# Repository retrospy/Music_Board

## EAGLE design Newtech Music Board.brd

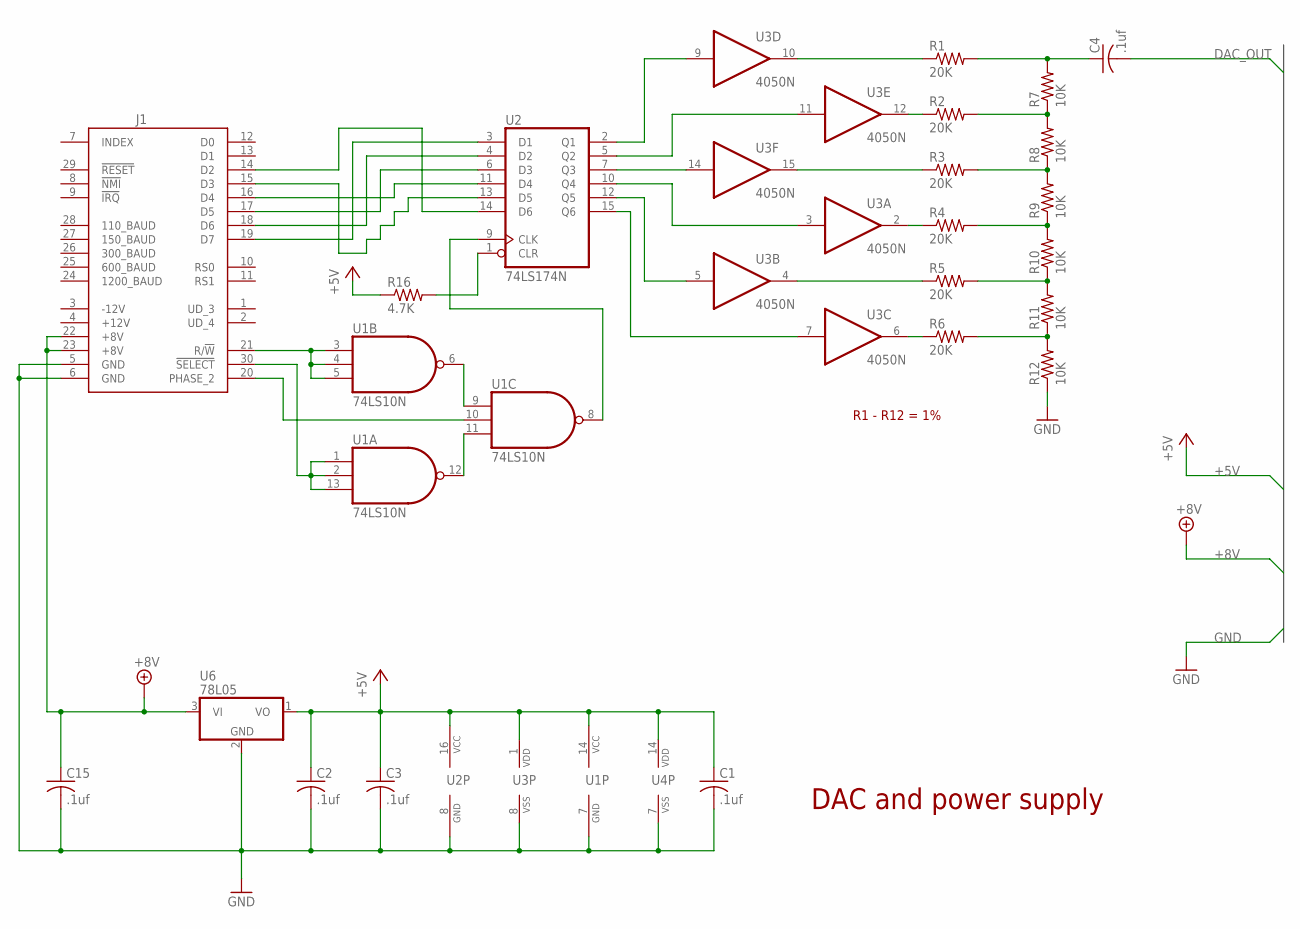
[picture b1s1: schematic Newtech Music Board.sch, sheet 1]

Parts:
C1, C2, C3, C15: .1uf; C025-025X050
C4: .1uf; C025-024X044
J1: SS-30_BOARD_CONNECTOR
R1, R2, R3, R4, R5, R6: 20K; 0204/7
R7, R8, R9, R10, R11, R12: 10K; 0204/7
R16: 4.7K; 0204/7
U1: 74LS10N; DIL14
U2: 74LS174N; DIL16
U3: 4050N; DIL16
U4: 4069N; DIL14
U6: 78L05; TO-92

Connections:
!SELECT: J1.30 (!SELECT), U1.1 (I0), U1.2 (I1), U1.13 (I2)
+5V: C1.1, C2.1, C3.1, R16.1, U1.14 (VCC), U2.16 (VCC), U3.1 (VDD), U4.14 (VDD), U6.1 (VO)
+8V: C15.1, J1.22 (+8V), J1.23 (+8V), U6.3 (VI); also elsewhere on the board
+12V: J1.4 (+12V)
-12V: J1.3 (-12V)
DAC_OUT: C4.2; also elsewhere on the board
GND: C1.2, C2.2, C3.2, C15.2, J1.5 (GND), J1.6 (GND), R12.1, U1.7 (GND), U2.8 (GND), U3.8 (VSS), U4.7 (VSS), U6.2 (GND); also elsewhere on the board
unnamed: J1.19 (D7), U2.3 (D1)
unnamed: J1.18 (D6), U2.4 (D2)
unnamed: J1.17 (D5), U2.6 (D3)
unnamed: U1.6 (O), U1.9 (I0)
unnamed: U1.11 (I2), U1.12 (O)
unnamed: J1.16 (D4), U2.11 (D4)
unnamed: J1.15 (D3), U2.13 (D5)
unnamed: J1.14 (D2), U2.14 (D6)
unnamed: U2.2 (Q1), U3.9 (I)
unnamed: U2.5 (Q2), U3.11 (I)
unnamed: U2.7 (Q3), U3.14 (I)
unnamed: U2.10 (Q4), U3.3 (I)
unnamed: U2.12 (Q5), U3.5 (I)
unnamed: U2.15 (Q6), U3.7 (I)
unnamed: U1.8 (O), U2.9 (CLK)
unnamed: R16.2, U2.1 (CLR)
unnamed: R1.1, U3.10 (O)
unnamed: R2.1, U3.12 (O)
unnamed: R3.1, U3.15 (O)
unnamed: R4.1, U3.2 (O)
unnamed: R5.1, U3.4 (O)
unnamed: R6.1, U3.6 (O)
unnamed: R2.2, R7.1, R8.2
unnamed: R3.2, R8.1, R9.2
unnamed: R4.2, R9.1, R10.2
unnamed: R5.2, R10.1, R11.2
unnamed: R6.2, R11.1, R12.2
unnamed: C4.1, R1.2, R7.2
PHASE2: J1.20 (PHASE_2), U1.10 (I1)
R/!W: J1.21 (R/!W), U1.3 (I0), U1.4 (I1), U1.5 (I2)

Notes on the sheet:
DAC and power supply
R1 - R12 = 1%

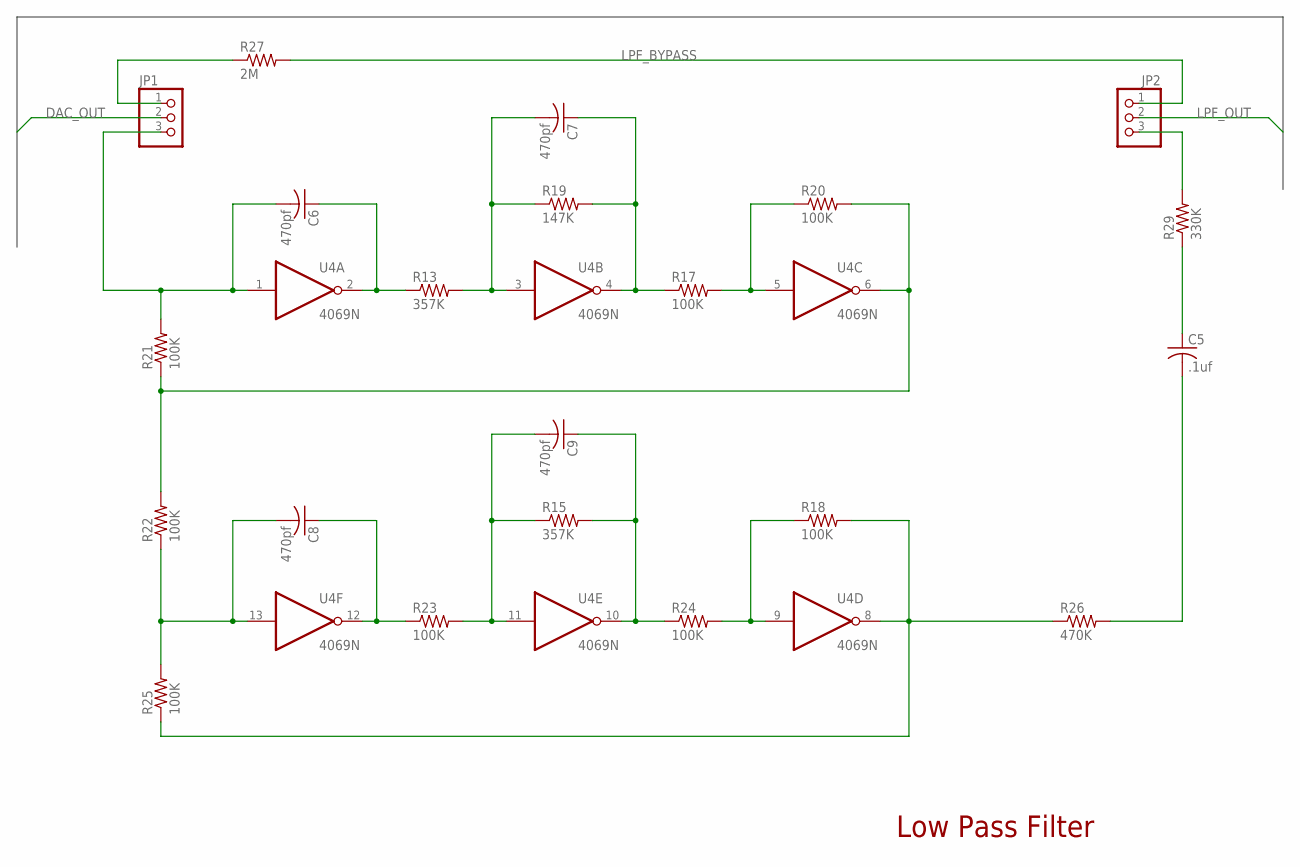
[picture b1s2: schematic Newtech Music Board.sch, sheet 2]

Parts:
C5: .1uf; C025-025X050
C6, C7, C8, C9: 470pf; C050-045X075
JP1, JP2: PINHD-1X3; 1X03
R13, R15: 357K; 0204/7
R17, R18, R20, R21, R22, R23, R24, R25: 100K; 0204/7
R19: 147K; 0204/7
R26: 470K; 0204/7
R27: 2M; 0204/7
R29: 330K; 0204/7
U4: 4069N; DIL14

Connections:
DAC_OUT: JP1.2; also elsewhere on the board
LPF_BYPASS: JP2.1, R27.2
LPF_OUT: JP2.2; also elsewhere on the board
unnamed: C6.2, JP1.3, R21.2, U4.1 (I)
unnamed: JP2.3, R29.2
unnamed: C6.1, R13.1, U4.2 (O)
unnamed: C7.2, R13.2, R19.1, U4.3 (I)
unnamed: C7.1, R17.1, R19.2, U4.4 (O)
unnamed: R17.2, R20.1, U4.5 (I)
unnamed: R20.2, R21.1, R22.2, U4.6 (O)
unnamed: JP1.1, R27.1
unnamed: C8.1, R23.1, U4.12 (O)
unnamed: C9.2, R15.1, R23.2, U4.11 (I)
unnamed: C9.1, R15.2, R24.1, U4.10 (O)
unnamed: R18.1, R24.2, U4.9 (I)
unnamed: R18.2, R25.1, R26.1, U4.8 (O)
unnamed: C5.2, R26.2
unnamed: C5.1, R29.1
unnamed: C8.2, R22.1, R25.2, U4.13 (I)

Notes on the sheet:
Low Pass Filter

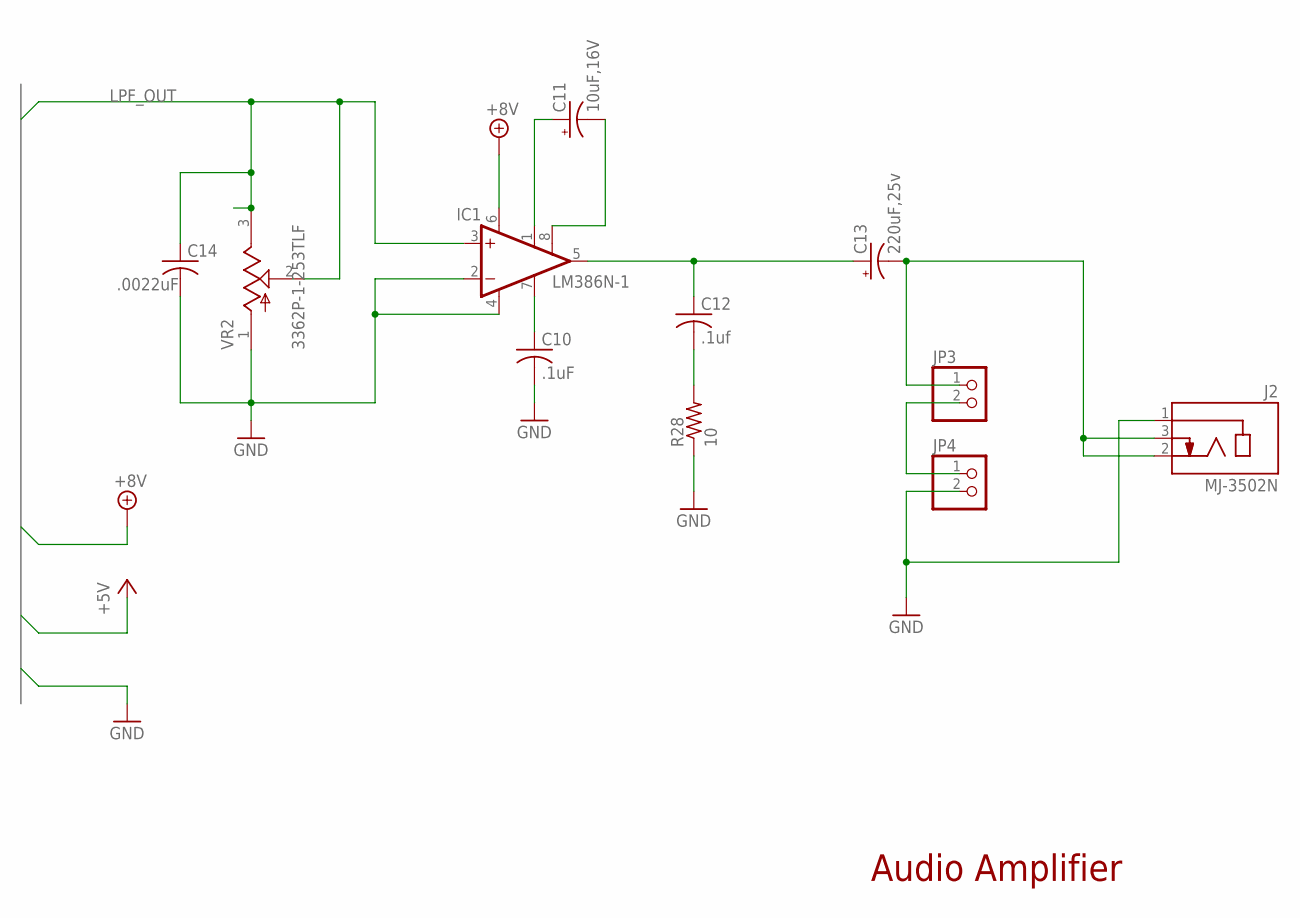
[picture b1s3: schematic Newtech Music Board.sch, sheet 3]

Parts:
C10: .1uF; C025-025X050
C11: 10uF,16V; E2,5-6
C12: .1uf; C025-025X050
C13: 220uF,25v; E25-9
C14: .0022uF; C025-025X050
IC1: LM386N-1; DIL08
J2: MJ-3502N; CUI_MJ-3502N
JP3, JP4: PINHD-1X2; 1X02
R28: 10; 0204/7
VR2: 3362P-1-253TLF; TRIM_3362P-1-253TLF

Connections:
+8V: IC1.6 (VS); also elsewhere on the board
GND: C10.2, C14.2, IC1.2 (-IN), IC1.4 (GND), J2.1, JP4.2, R28.1, VR2.1 (CCW); also elsewhere on the board
LPF_OUT: C14.1, IC1.3 (+IN), VR2.2 (WIPER), VR2.3 (CW); also elsewhere on the board
unnamed: JP3.2, JP4.1
unnamed: C10.1, IC1.7 (BYPASS)
unnamed: C12.2, R28.2
unnamed: C11.+, IC1.1 (GAIN)
unnamed: C12.1, C13.+, IC1.5 (OUT)
unnamed: C13.-, J2.2, J2.3, JP3.1
unnamed: C11.-, IC1.8 (GAIN)

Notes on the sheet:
Audio Amplifier

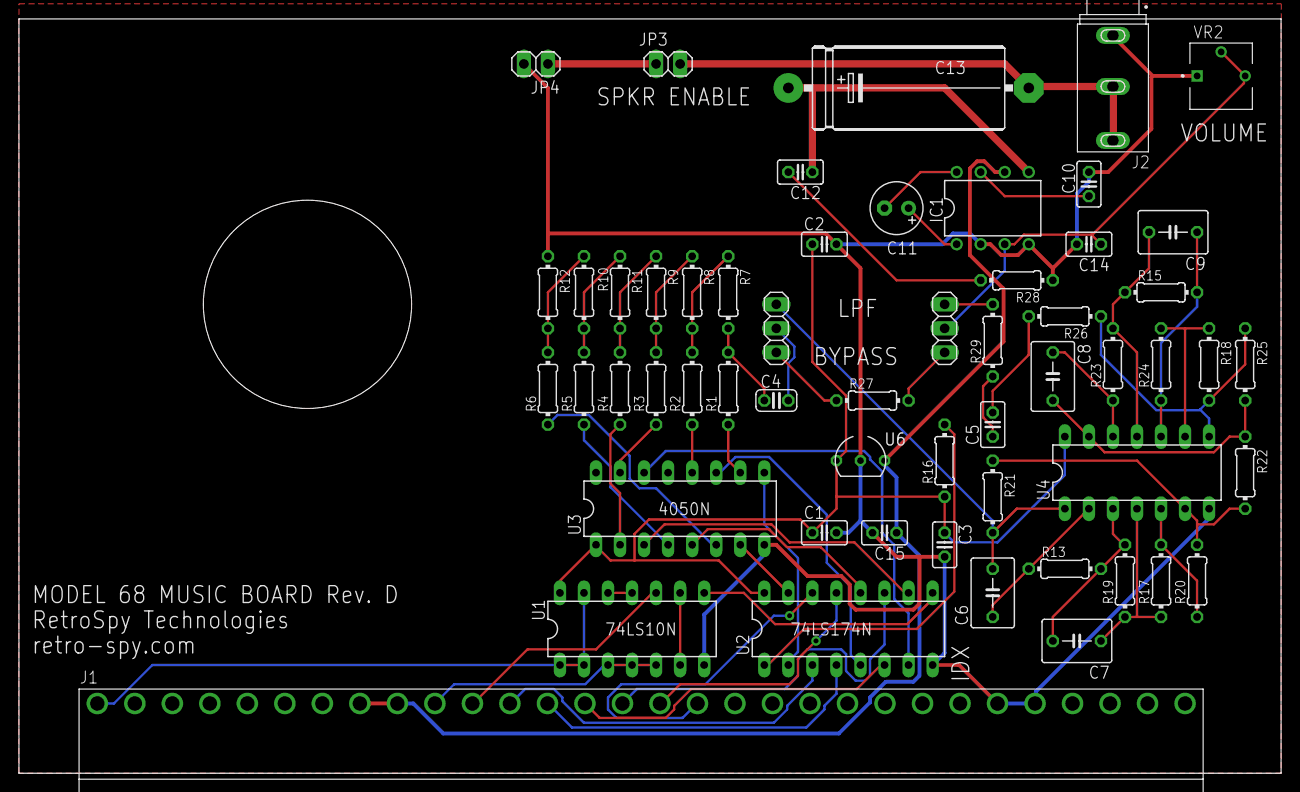
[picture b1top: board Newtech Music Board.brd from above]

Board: 2 copper layers, 133.3 x 79.7 mm, 56 parts (0 on the bottom side), 60 nets.

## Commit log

2023-10-03 Updated Speaker and incorrect resistor value
2023-10-10 Added headphone jack out
2024-03-26 Put real speaker on
2024-03-29 Matched the circuit to the S-100 Board
2024-03-29 Put back the LM386
2024-04-03 Modifcations for prototype
2024-07-10 Redid the DAC routing
2024-07-17 Rearranged ICs to try and fix stuttering
2024-07-18 Fixed the mixed up D7 and D5 lines

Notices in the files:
parts and their libraries:
SparkFun: Licensing: CC v3.0 Share-Alike You are welcome to use this library for commercial purposes.
